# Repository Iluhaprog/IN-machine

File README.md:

> [!NOTE]
> Данный проект является учебным и предназначен в первую очередь для того
> чтобы разобраться и понять как работает вычислительное устройство на самом 
> низком уровне.

В данный момент проект на стадии разработки печатных плат и сборки физического 
устройства. 

Сейчас уже созданы и заказанны платы для АЛУ и Регистра флагов.

В процессе создания блок пользовательских регистров и счетчики команд и микро команд.

Сейчас в планы входят:
- [ ] - доработать схему управляющего устройства для работы с LCD 12864 экраном по SPI
- [ ] - разработка платы расширения для того, чтобы данное вычислительно устройство могло работать с датчиками.
- [ ] - изучение возможностей данного устройства и его параметров

Более подробно о базовых возможностях данного вычислительного устройства можно узнать в директории docs/

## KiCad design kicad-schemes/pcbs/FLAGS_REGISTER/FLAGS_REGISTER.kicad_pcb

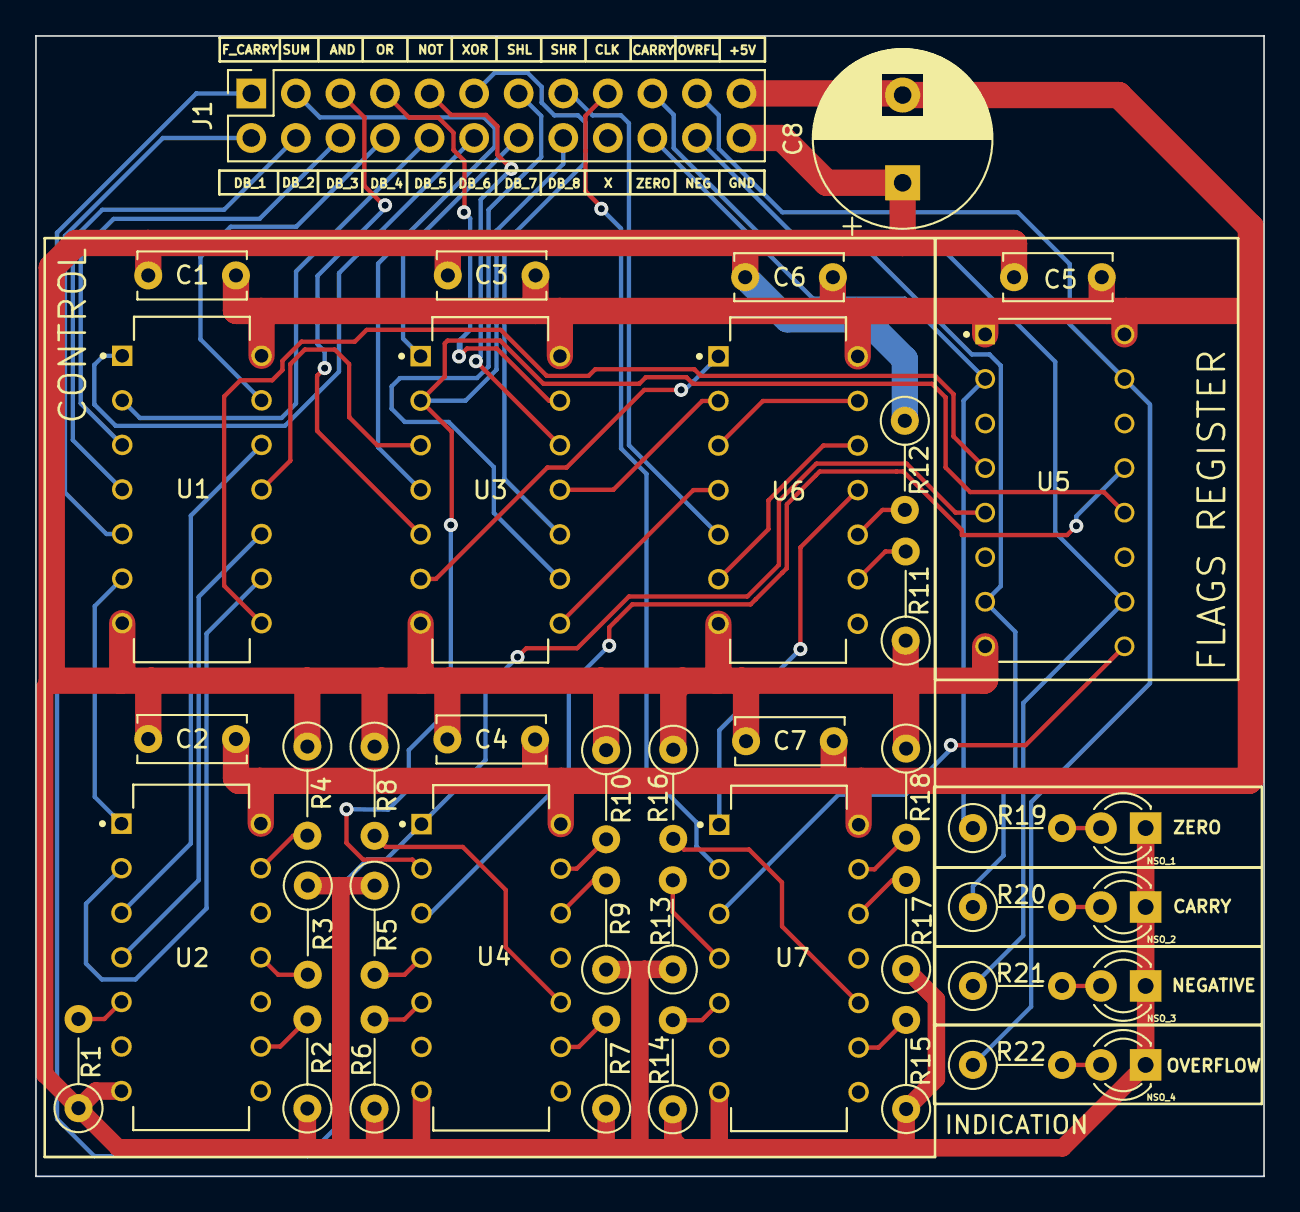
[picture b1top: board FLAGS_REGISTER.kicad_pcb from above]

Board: 2 copper layers, 70.0 x 65.0 mm, 42 parts (0 on the bottom side), 59 nets.

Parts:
C1, C2, C3, C4, C5, C6, C7: C; C_Disc_D6.0mm_W2.5mm_P5.00mm
C8: C; CP_Radial_D10.0mm_P5.00mm
J1: Conn_02x12_Odd_Even; PinSocket_2x12_P2.54mm_Vertical
NSO_1, NSO_2, NSO_3, NSO_4: LED; LED_D3.0mm
R1, R2, R3, R4, R5, R6, R7, R8, R9, R10, R11, R12, R13, R14, R15, R16, R17, R18, R19, R20, R21, R22: R; R_Axial_DIN0207_L6.3mm_D2.5mm_P5.08mm_Vertical
U1: SN74HC27N; DIP794W45P254L1969H508Q14
U2: SN74HC14N; DIP794W45P254L1969H508Q14
U3, U6: SN74HC32N; DIP794W45P254L1969H508Q14
U4: SN74HC86N; DIP794W45P254L1969H508Q14
U5: SN74HC175N; DIP794W45P254L1969H508Q16
U7: SN74HC08N; DIP794W45P254L1969H508Q14

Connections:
+5V: C1.2, C2.2, C3.2, C4.2, C5.2, C6.2, C7.2, C8.2, J1.23, U1.14 (VCC), U2.14 (VCC), U3.14 (VCC), U4.14 (VCC), U5.1 (~CLR), U5.16 (VCC), U6.14 (VCC), U7.14 (VCC)
/CARRY: J1.19, R20.1, U5.7 (2Q)
/CLK: J1.17, U7.2 (1B)
/DB_1: J1.2, U1.5 (2C)
/DB_2: J1.4, U1.4 (2B)
/DB_3: J1.6, U1.3 (2A)
/DB_4: J1.8, U1.13 (1C)
/DB_5: J1.10, U1.2 (1B)
/DB_6: J1.12, U1.1 (1A)
/DB_7: J1.14, U3.1 (1A)
/DB_8: J1.16, U3.2 (1B), U4.2 (1B), U5.12 (3D)
/F_CARRY: J1.1, U4.1 (1A), U5.5 (2D)
/NEGATIVE: J1.22, R21.1, U5.10 (3Q)
/OVERFLOW: J1.21, R22.1, U5.15 (4Q)
/ZERO: J1.20, R19.1, U5.2 (1Q)
/n_AND_EN: J1.5, U3.5 (2B)
/n_NOT_EN: J1.9, U3.12 (4A)
/n_OR_EN: J1.7, U3.13 (4B)
/n_SHL_EN: J1.13, U3.9 (3A)
/n_SHR_EN: J1.15, U6.5 (2B)
/n_SUM_EN: J1.3, U3.4 (2A)
/n_XOR_EN: J1.11, U3.10 (3B)
CLK_FLAGS: U5.9 (CLK), U7.3 (1Y)
EN_WRITE_FLAGS: U6.11 (4Y), U7.1 (1A)
F_OVERFLOW: U4.3 (1Y), U5.13 (4D)
F_ZERO: U1.8 (3Y), U5.4 (1D)
GND: C1.1, C2.1, C3.1, C4.1, C5.1, C6.1, C7.1, C8.1, J1.24, NSO_1.1 (K), NSO_2.1 (K), NSO_3.1 (K), NSO_4.1 (K), R1.1, R2.1, R3.1, R4.1, R5.1, R6.1, R7.1, R8.1, R9.1, R10.1, R11.1, R12.1, R13.1, R14.1, R15.1, R16.1, R17.1, R18.1, U1.7 (GND), U2.7 (GND), U3.7 (GND), U4.7 (GND), U5.8 (GND), U6.7 (GND), U7.7 (GND)
NOT_OR_OR: U3.11 (4Y), U6.2 (1B)
unnamed: NSO_1.2 (A), R19.2
unnamed: NSO_2.2 (A), R20.2
unnamed: NSO_3.2 (A), R21.2
unnamed: NSO_4.2 (A), R22.2
unnamed: R1.2, U2.5 (3A)
unnamed: R2.2, U2.9 (4A)
unnamed: R3.2, U2.11 (5A)
unnamed: R4.2, U2.13 (6A)
unnamed: R5.2, U4.4 (2A)
unnamed: R6.2, U4.5 (2B)
unnamed: R7.2, U4.9 (3A)
unnamed: R8.2, U4.10 (3B)
unnamed: R9.2, U4.12 (4A)
unnamed: R10.2, U4.13 (4B)
unnamed: R11.2, U6.9 (3A)
unnamed: R12.2, U6.10 (3B)
unnamed: R13.2, U7.4 (2A)
unnamed: R14.2, U7.5 (2B)
unnamed: R15.2, U7.9 (3A)
unnamed: R16.2, U7.10 (3B)
unnamed: R17.2, U7.12 (4A)
unnamed: R18.2, U7.13 (4B)
O1_O2_O3: U1.6 (2Y), U2.1 (1A)
O4_O5_O6: U1.12 (1Y), U2.3 (2A)
SUM_OR_AND: U3.6 (2Y), U6.1 (1A)
SUM_OR_AND_OR_NOT_OR_OR: U6.3 (1Y), U6.13 (4B)
XOR_OR_SHL: U3.8 (3Y), U6.4 (2A)
XOR_OR_SHL_OR_SHR: U6.6 (2Y), U6.12 (4A)
n_O1_O2_O3: U1.9 (3A), U2.2 (1Y)
n_O4_O5_O6: U1.10 (3B), U2.4 (2Y)
n_O7_O8: U1.11 (3C), U3.3 (1Y)

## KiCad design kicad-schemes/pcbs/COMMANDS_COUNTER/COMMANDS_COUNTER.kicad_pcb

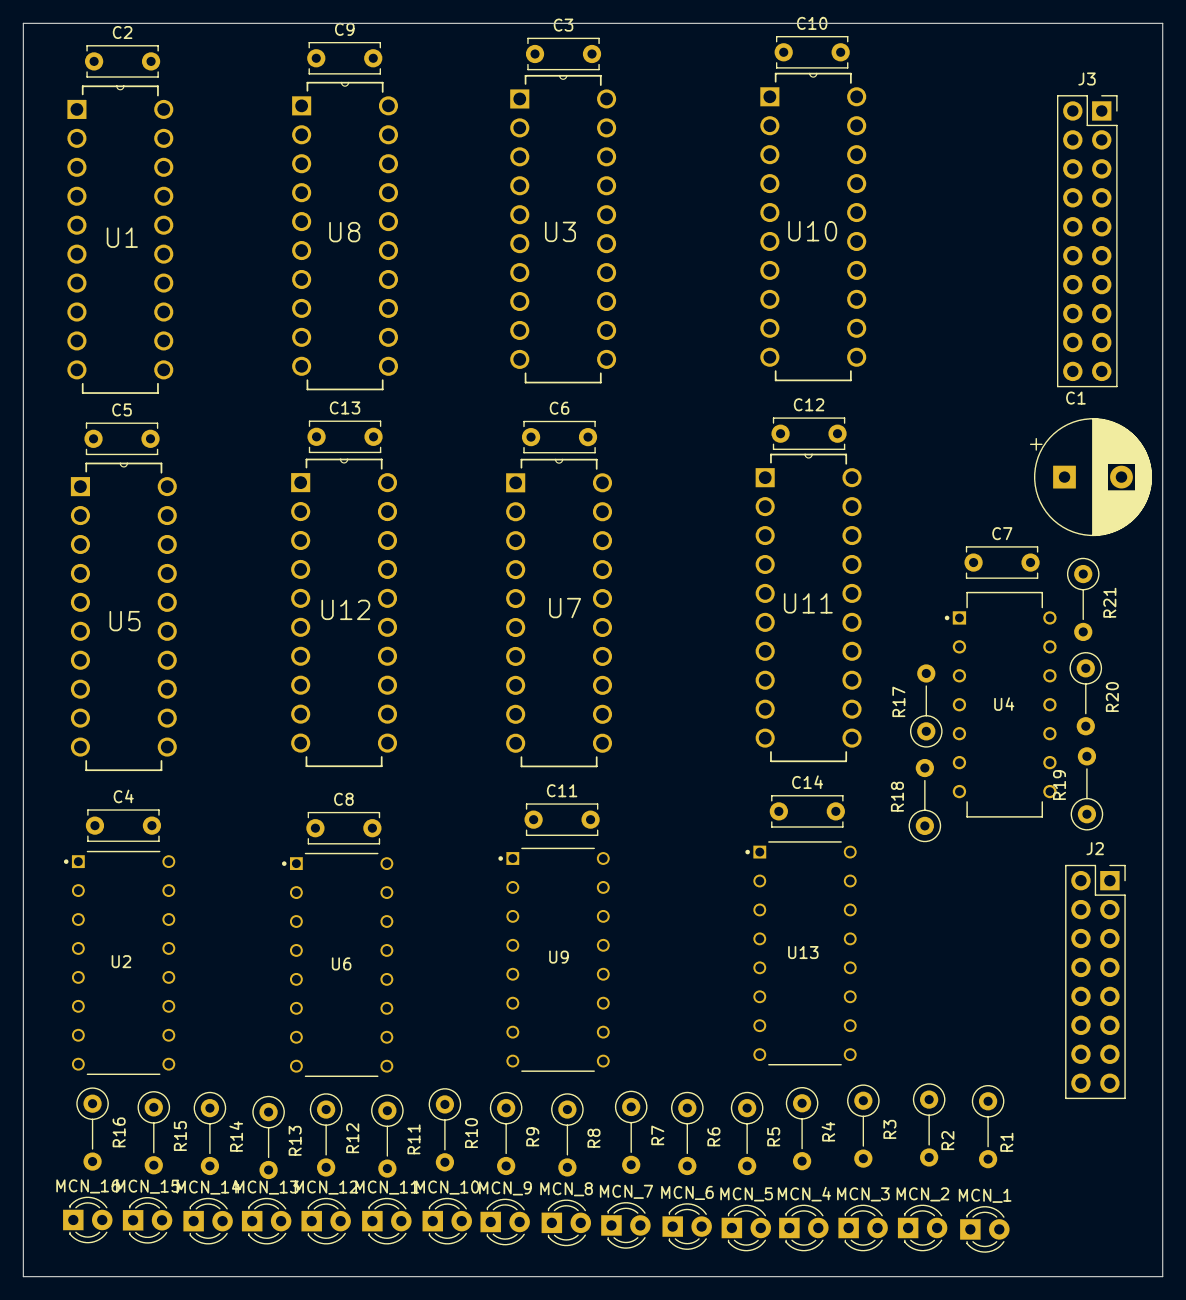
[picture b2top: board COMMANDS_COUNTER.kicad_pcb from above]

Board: 2 copper layers, 100.0 x 110.0 mm, 66 parts (0 on the bottom side), 109 nets, no tracks yet.

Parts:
C1: C; CP_Radial_D10.0mm_P5.00mm
C2, C3, C4, C5, C6, C7, C8, C9, C10, C11, C12, C13, C14: C; C_Disc_D6.0mm_W2.5mm_P5.00mm
J2: Conn_02x08_Odd_Even; PinSocket_2x08_P2.54mm_Vertical
J3: Conn_02x10_Odd_Even; PinSocket_2x10_P2.54mm_Vertical
MCN_1, MCN_2, MCN_3, MCN_4, MCN_5, MCN_6, MCN_7, MCN_8, MCN_9, MCN_10, MCN_11, MCN_12, MCN_13, MCN_14, MCN_15, MCN_16: LED; LED_D3.0mm
R1, R2, R3, R4, R5, R6, R7, R8, R9, R10, R11, R12, R13, R14, R15, R16, R17, R18, R19, R20, R21: R; R_Axial_DIN0207_L6.3mm_D2.5mm_P5.08mm_Vertical
U1, U3, U8, U10: SN74HC377N; DIP254P762X508-20
U2, U6, U9, U13: SN74HC163N; DIP794W45P254L1969H508Q16
U4: SN74HC14N; DIP794W45P254L1969H508Q14
U5, U7, U11, U12: SN74HC244N; DIP254P762X508-20

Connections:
/AB1: J2.1, R1.1, U2.14 (QA), U3.3 (1D)
/AB2: J2.3, R2.1, U2.13 (QB), U3.4 (2D)
/AB3: J2.5, R3.1, U2.12 (QC), U3.7 (3D)
/AB4: J2.7, R4.1, U2.11 (QD), U3.8 (4D)
/AB5: J2.9, R5.1, U3.13 (5D), U6.14 (QA)
/AB6: J2.11, R6.1, U3.14 (6D), U6.13 (QB)
/AB7: J2.13, R7.1, U3.17 (7D), U6.12 (QC)
/AB8: J2.15, R8.1, U3.18 (8D), U6.11 (QD)
/AB9: J2.2, R9.1, U9.14 (QA), U10.3 (1D)
/AB10: J2.4, R10.1, U9.13 (QB), U10.4 (2D)
/AB11: J2.6, R11.1, U9.12 (QC), U10.7 (3D)
/AB12: J2.8, R12.1, U9.11 (QD), U10.8 (4D)
/AB13: J2.10, R13.1, U10.13 (5D), U13.14 (QA)
/AB14: J2.12, R14.1, U10.14 (6D), U13.13 (QB)
/AB15: J2.14, R15.1, U10.17 (7D), U13.12 (QC)
/AB16: J2.16, R16.1, U10.18 (8D), U13.11 (QD)
/CAR_n_EN1: J3.18, U3.1 (~CLKEN)
/CAR_n_EN2: J3.20, U10.1 (~CLKEN)
/CAR_n_EN_Out: J3.16, U7.1 (1~OE), U7.19 (2~OE), U11.1 (1~OE), U11.19 (2~OE)
/C_n_Clear: J3.4, U2.1 (~CLR), U6.1 (~CLR), U9.1 (~CLR), U13.1 (~CLR)
/C_n_Enable_Counter: J3.2, U2.7 (ENP), U6.7 (ENP), U9.7 (ENP), U13.7 (ENP)
/C_n_Enable_Load: J3.6, U2.9 (~LOAD), U6.9 (~LOAD), U9.9 (~LOAD), U13.9 (~LOAD)
/DB1: J3.5, U1.13 (5D), U8.13 (5D)
/DB2: J3.7, U1.8 (4D), U8.8 (4D)
/DB3: J3.9, U1.14 (6D), U8.14 (6D)
/DB4: J3.11, U1.7 (3D), U8.7 (3D)
/DB5: J3.13, U1.17 (7D), U8.17 (7D)
/DB6: J3.15, U1.4 (2D), U8.4 (2D)
/DB7: J3.17, U1.18 (8D), U8.18 (8D)
/DB8: J3.19, U1.3 (1D), U8.3 (1D)
/GND: C1.1, C2.1, C3.1, C4.1, C5.1, C6.1, C7.1, C8.1, C9.1, C10.1, C11.1, C12.1, C13.1, C14.1, J3.1, MCN_1.1 (K), MCN_2.1 (K), MCN_3.1 (K), MCN_4.1 (K), MCN_5.1 (K), MCN_6.1 (K), MCN_7.1 (K), MCN_8.1 (K), MCN_9.1 (K), MCN_10.1 (K), MCN_11.1 (K), MCN_12.1 (K), MCN_13.1 (K), MCN_14.1 (K), MCN_15.1 (K), MCN_16.1 (K), R17.1, R18.1, R19.1, R20.1, R21.1, U1.10 (GND), U2.8 (GND), U3.10 (GND), U4.7 (GND), U5.10 (GND), U6.8 (GND), U7.10 (GND), U8.10 (GND), U9.8 (GND), U10.10 (GND), U11.10 (GND), U12.10 (GND), U13.8 (GND)
/POWER: C1.2, C2.2, C3.2, C4.2, C5.2, C6.2, C7.2, C8.2, C9.2, C10.2, C11.2, C12.2, C13.2, C14.2, J3.3, U1.20 (VCC), U2.10 (ENT), U2.16 (VCC), U3.20 (VCC), U4.14 (VCC), U5.20 (VCC), U6.16 (VCC), U7.20 (VCC), U8.20 (VCC), U9.16 (VCC), U10.20 (VCC), U11.20 (VCC), U12.20 (VCC), U13.16 (VCC)
/UAR_n_EN1: J3.8, U1.1 (~CLKEN)
/UAR_n_EN2: J3.10, U8.1 (~CLKEN)
/UAR_n_EN_Out: J3.12, U5.1 (1~OE), U5.19 (2~OE), U12.1 (1~OE), U12.19 (2~OE)
CLK: J3.14, U1.11 (CLK), U2.2 (CLK), U4.1 (1A), U6.2 (CLK), U8.11 (CLK), U9.2 (CLK), U13.2 (CLK)
CR_O_1: U2.3 (A), U5.3 (2Y4), U7.18 (1Y1)
CR_O_2: U2.4 (B), U5.18 (1Y1), U7.16 (1Y2)
CR_O_3: U2.5 (C), U5.5 (2Y3), U7.14 (1Y3)
CR_O_4: U2.6 (D), U5.16 (1Y2), U7.12 (1Y4)
CR_O_5: U5.7 (2Y2), U6.3 (A), U7.9 (2Y1)
CR_O_6: U5.14 (1Y3), U6.4 (B), U7.7 (2Y2)
CR_O_7: U5.9 (2Y1), U6.5 (C), U7.5 (2Y3)
CR_O_8: U5.12 (1Y4), U6.6 (D), U7.3 (2Y4)
CR_O_9: U9.3 (A), U11.18 (1Y1), U12.3 (2Y4)
CR_O_10: U9.4 (B), U11.16 (1Y2), U12.18 (1Y1)
CR_O_11: U9.5 (C), U11.14 (1Y3), U12.5 (2Y3)
CR_O_12: U9.6 (D), U11.12 (1Y4), U12.16 (1Y2)
CR_O_13: U11.9 (2Y1), U12.7 (2Y2), U13.3 (A)
CR_O_14: U11.7 (2Y2), U12.14 (1Y3), U13.4 (B)
CR_O_15: U11.5 (2Y3), U12.9 (2Y1), U13.5 (C)
CR_O_16: U11.3 (2Y4), U12.12 (1Y4), U13.6 (D)
C_RCO_1: U2.15 (RCO), U6.10 (ENT)
C_RCO_2: U6.15 (RCO), U9.10 (ENT)
C_RCO_3: U9.15 (RCO), U13.10 (ENT)
unnamed: MCN_1.2 (A), R1.2
unnamed: MCN_2.2 (A), R2.2
unnamed: MCN_3.2 (A), R3.2
unnamed: MCN_4.2 (A), R4.2
unnamed: MCN_5.2 (A), R5.2
unnamed: MCN_6.2 (A), R6.2
unnamed: MCN_7.2 (A), R7.2
unnamed: MCN_8.2 (A), R8.2
unnamed: MCN_9.2 (A), R9.2
unnamed: MCN_10.2 (A), R10.2
unnamed: MCN_11.2 (A), R11.2
unnamed: MCN_12.2 (A), R12.2
unnamed: MCN_13.2 (A), R13.2
unnamed: MCN_14.2 (A), R14.2
unnamed: MCN_15.2 (A), R15.2
unnamed: MCN_16.2 (A), R16.2
unnamed: R17.2, U4.3 (2A)
unnamed: R18.2, U4.5 (3A)
unnamed: R19.2, U4.9 (4A)
unnamed: R20.2, U4.11 (5A)
unnamed: R21.2, U4.13 (6A)
in_UAR_O_1: U1.12 (5Q), U5.17 (2A4)
in_UAR_O_2: U1.9 (4Q), U5.2 (1A1)
in_UAR_O_3: U1.15 (6Q), U5.15 (2A3)
in_UAR_O_4: U1.6 (3Q), U5.4 (1A2)
in_UAR_O_5: U1.16 (7Q), U5.13 (2A2)
in_UAR_O_6: U1.5 (2Q), U5.6 (1A3)
in_UAR_O_7: U1.19 (8Q), U5.11 (2A1)
in_UAR_O_8: U1.2 (1Q), U5.8 (1A4)
in_UAR_O_9: U8.12 (5Q), U12.17 (2A4)
in_UAR_O_10: U8.9 (4Q), U12.2 (1A1)
in_UAR_O_11: U8.15 (6Q), U12.15 (2A3)
in_UAR_O_12: U8.6 (3Q), U12.4 (1A2)
in_UAR_O_13: U8.16 (7Q), U12.13 (2A2)
in_UAR_O_14: U8.5 (2Q), U12.6 (1A3)
in_UAR_O_15: U8.19 (8Q), U12.11 (2A1)
in_UAR_O_16: U8.2 (1Q), U12.8 (1A4)
in_СAR_O_1: U3.2 (1Q), U7.2 (1A1)
in_СAR_O_2: U3.5 (2Q), U7.4 (1A2)
in_СAR_O_3: U3.6 (3Q), U7.6 (1A3)
in_СAR_O_4: U3.9 (4Q), U7.8 (1A4)
in_СAR_O_5: U3.12 (5Q), U7.11 (2A1)
in_СAR_O_6: U3.15 (6Q), U7.13 (2A2)
in_СAR_O_7: U3.16 (7Q), U7.15 (2A3)
in_СAR_O_8: U3.19 (8Q), U7.17 (2A4)
in_СAR_O_9: U10.2 (1Q), U11.2 (1A1)
in_СAR_O_10: U10.5 (2Q), U11.4 (1A2)
in_СAR_O_11: U10.6 (3Q), U11.6 (1A3)
in_СAR_O_12: U10.9 (4Q), U11.8 (1A4)
in_СAR_O_13: U10.12 (5Q), U11.11 (2A1)
in_СAR_O_14: U10.15 (6Q), U11.13 (2A2)
in_СAR_O_15: U10.16 (7Q), U11.15 (2A3)
in_СAR_O_16: U10.19 (8Q), U11.17 (2A4)
n_CLK: U3.11 (CLK), U4.2 (1Y), U10.11 (CLK)

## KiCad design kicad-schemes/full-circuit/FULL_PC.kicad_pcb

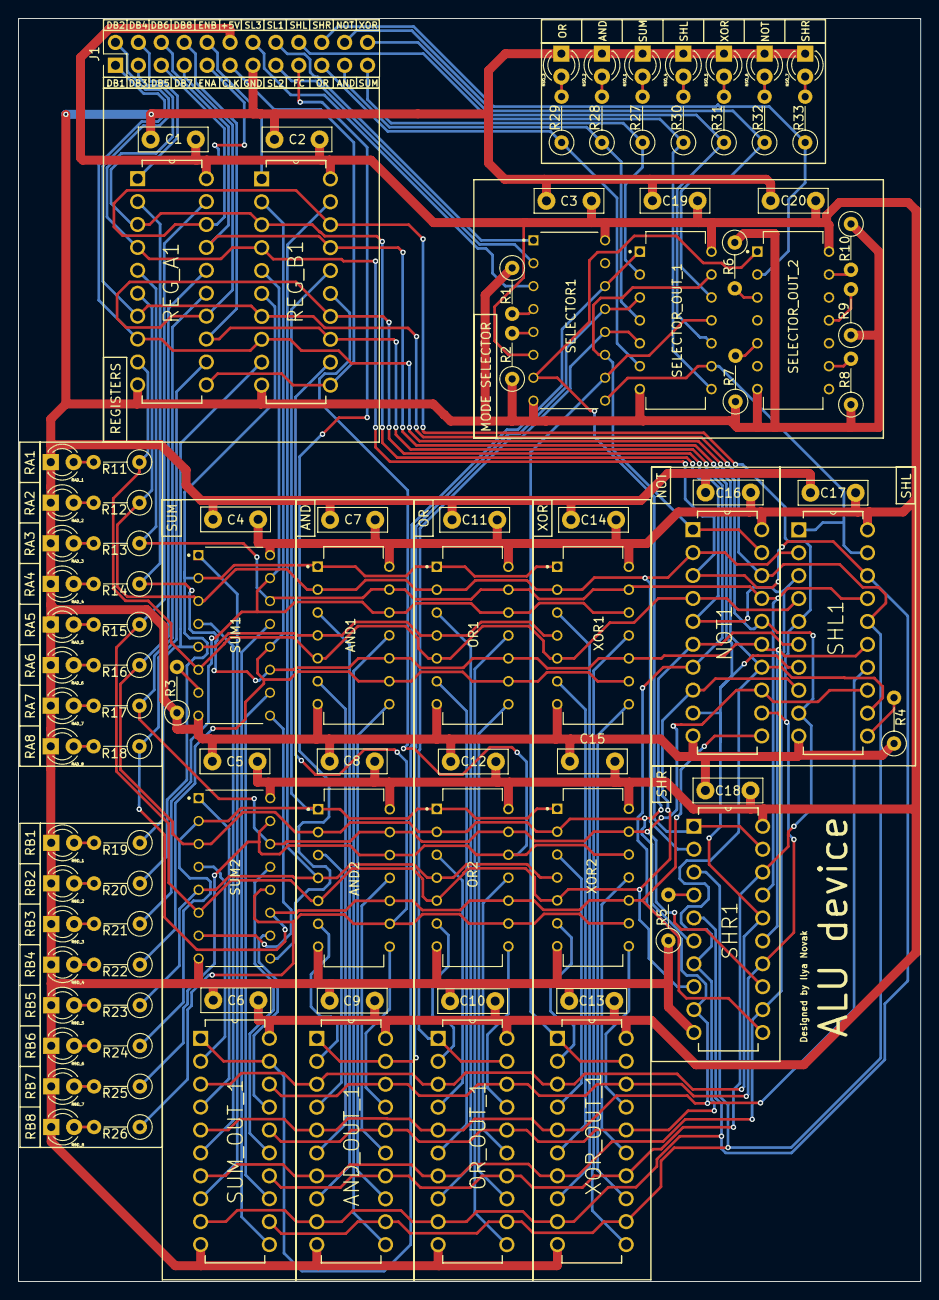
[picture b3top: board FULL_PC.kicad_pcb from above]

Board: 2 copper layers, 100.0 x 140.0 mm, 97 parts (0 on the bottom side), 113 nets.

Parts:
AND1, AND2: SN74HC08N; DIP794W45P254L1969H508Q14
AND_OUT_1: SN74HC244N; DIP254P762X508-20
C1, C2, C3, C4, C5, C6, C7, C8, C9, C10, C11, C12, C13, C14, C15, C16, C17, C18, C19, C20: C; C_Disc_D7.5mm_W2.5mm_P5.00mm
J1: Conn_02x12_Counter_Clockwise; PinHeader_2x12_P2.54mm_Vertical
NOT1: SN74HC240N; DIP254P762X508-20
NSO_1, NSO_2, NSO_3, NSO_4, NSO_5, NSO_6, NSO_7: LED; LED_D3.0mm
OR1, OR2: SN74HC32N; DIP794W45P254L1969H508Q14
OR_OUT_1: SN74HC244N; DIP254P762X508-20
R1, R2, R3, R4, R5, R6, R7, R8, R9, R10, R11, R12, R13, R14, R15, R16, R17, R18, R19, R20, R21, R22, R23, R24, R25, R26, R27, R28, R29, R30, R31, R32, R33: R; R_Axial_DIN0207_L6.3mm_D2.5mm_P5.08mm_Vertical
RAD_1, RAD_2, RAD_3, RAD_4, RAD_5, RAD_6, RAD_7, RAD_8: LED; LED_D3.0mm
RBD_1, RBD_2, RBD_3, RBD_4, RBD_5, RBD_6, RBD_7, RBD_8: LED; LED_D3.0mm
REG_A1: SN74HC377N; DIP254P762X508-20
REG_B1: SN74HC377N; DIP254P762X508-20
SELECTOR1: SN74HC138N; DIP794W45P254L1969H508Q16
SELECTOR_OUT_1, SELECTOR_OUT_2: SN74HC14N; DIP794W45P254L1969H508Q14
SHL1: SN74HC244N; DIP254P762X508-20
SHR1: SN74HC244N; DIP254P762X508-20
SUM1, SUM2: SN74HC283N; DIP794W45P254L1969H508Q16
SUM_OUT_1: SN74HC244N; DIP254P762X508-20
XOR1, XOR2: SN74HC86N; DIP794W45P254L1969H508Q14
XOR_OUT_1: SN74HC244N; DIP254P762X508-20

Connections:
+5V: AND1.14 (VCC), AND2.14 (VCC), AND_OUT_1.20 (VCC), C1.2, C2.2, C3.2, C4.2, C5.2, C6.2, C7.2, C8.2, C9.2, C10.2, C11.2, C12.2, C13.2, C14.2, C15.2, C16.2, C17.2, C18.2, C19.2, C20.2, J1.12, NOT1.20 (VCC), OR1.14 (VCC), OR2.14 (VCC), OR_OUT_1.20 (VCC), REG_A1.20 (VCC), REG_B1.20 (VCC), SELECTOR1.6 (G1), SELECTOR1.16 (VCC), SELECTOR_OUT_1.14 (VCC), SELECTOR_OUT_2.14 (VCC), SHL1.20 (VCC), SHR1.20 (VCC), SUM1.16 (Vcc), SUM2.16 (Vcc), SUM_OUT_1.20 (VCC), XOR1.14 (VCC), XOR2.14 (VCC), XOR_OUT_1.20 (VCC)
/ALU/CLK: J1.11, REG_A1.11 (CLK), REG_B1.11 (CLK)
/ALU/DB_1: AND_OUT_1.14 (1Y3), J1.1, NOT1.16 (1Y2), OR_OUT_1.14 (1Y3), REG_A1.8 (4D), REG_B1.8 (4D), SHL1.9 (2Y1), SHR1.18 (1Y1), SUM_OUT_1.14 (1Y3), XOR_OUT_1.14 (1Y3)
/ALU/DB_2: AND_OUT_1.12 (1Y4), J1.2, NOT1.18 (1Y1), OR_OUT_1.12 (1Y4), REG_A1.7 (3D), REG_B1.7 (3D), SHL1.16 (1Y2), SHR1.3 (2Y4), SUM_OUT_1.12 (1Y4), XOR_OUT_1.12 (1Y4)
/ALU/DB_3: AND_OUT_1.9 (2Y1), J1.3, NOT1.3 (2Y4), OR_OUT_1.9 (2Y1), REG_A1.4 (2D), REG_B1.4 (2D), SHL1.18 (1Y1), SHR1.5 (2Y3), SUM_OUT_1.9 (2Y1), XOR_OUT_1.9 (2Y1)
/ALU/DB_4: AND_OUT_1.7 (2Y2), J1.4, NOT1.5 (2Y3), OR_OUT_1.7 (2Y2), REG_A1.3 (1D), REG_B1.3 (1D), SHL1.3 (2Y4), SHR1.12 (1Y4), SUM_OUT_1.7 (2Y2), XOR_OUT_1.7 (2Y2)
/ALU/DB_5: AND_OUT_1.18 (1Y1), J1.5, NOT1.12 (1Y4), OR_OUT_1.18 (1Y1), REG_A1.18 (8D), REG_B1.18 (8D), SHL1.5 (2Y3), SHR1.14 (1Y3), SUM_OUT_1.18 (1Y1), XOR_OUT_1.18 (1Y1)
/ALU/DB_6: AND_OUT_1.16 (1Y2), J1.6, NOT1.14 (1Y3), OR_OUT_1.16 (1Y2), REG_A1.17 (7D), REG_B1.17 (7D), SHL1.12 (1Y4), SHR1.7 (2Y2), SUM_OUT_1.16 (1Y2), XOR_OUT_1.16 (1Y2)
/ALU/DB_7: AND_OUT_1.5 (2Y3), J1.7, NOT1.7 (2Y2), OR_OUT_1.5 (2Y3), REG_A1.14 (6D), REG_B1.14 (6D), SHL1.14 (1Y3), SHR1.9 (2Y1), SUM_OUT_1.5 (2Y3), XOR_OUT_1.5 (2Y3)
/ALU/DB_8: AND_OUT_1.3 (2Y4), J1.8, NOT1.9 (2Y1), OR_OUT_1.3 (2Y4), REG_A1.13 (5D), REG_B1.13 (5D), SHL1.7 (2Y2), SHR1.16 (1Y2), SUM_OUT_1.3 (2Y4), XOR_OUT_1.3 (2Y4)
/ALU/EN_A: J1.9, REG_A1.1 (~CLKEN)
/ALU/EN_B: J1.10, REG_B1.1 (~CLKEN)
/ALU/F_CARRY: J1.17, SUM2.9 (C4)
/ALU/SL_1: J1.16, SELECTOR1.1 (A)
/ALU/SL_2: J1.15, SELECTOR1.2 (B)
/ALU/SL_3: J1.14, SELECTOR1.3 (C)
/ALU/n_AND_EN: J1.21, R28.1, SELECTOR_OUT_1.4 (2Y)
/ALU/n_NOT_EN: J1.22, R32.1, SELECTOR_OUT_1.12 (6Y)
/ALU/n_OR_EN: J1.19, R29.1, SELECTOR_OUT_1.6 (3Y)
/ALU/n_SHL_EN: J1.18, R30.1, SELECTOR_OUT_1.8 (4Y)
/ALU/n_SHR_EN: J1.20, R33.1, SELECTOR_OUT_2.2 (1Y)
/ALU/n_SUM_EN: J1.23, R27.1, SELECTOR_OUT_1.2 (1Y)
/ALU/n_XOR_EN: J1.24, R31.1, SELECTOR_OUT_1.10 (5Y)
AND_EN: AND_OUT_1.1 (1~OE), AND_OUT_1.19 (2~OE), SELECTOR1.13 (Y2), SELECTOR_OUT_1.3 (2A)
AND_O_1: AND1.6 (2Y), AND_OUT_1.6 (1A3)
AND_O_2: AND1.3 (1Y), AND_OUT_1.8 (1A4)
AND_O_3: AND1.11 (4Y), AND_OUT_1.11 (2A1)
AND_O_4: AND1.8 (3Y), AND_OUT_1.13 (2A2)
AND_O_5: AND2.6 (2Y), AND_OUT_1.2 (1A1)
AND_O_6: AND2.3 (1Y), AND_OUT_1.4 (1A2)
AND_O_7: AND2.11 (4Y), AND_OUT_1.15 (2A3)
AND_O_8: AND2.8 (3Y), AND_OUT_1.17 (2A4)
GND: AND1.7 (GND), AND2.7 (GND), AND_OUT_1.10 (GND), C1.1, C2.1, C3.1, C4.1, C5.1, C6.1, C7.1, C8.1, C9.1, C10.1, C11.1, C12.1, C13.1, C14.1, C15.1, C16.1, C17.1, C18.1, C19.1, C20.1, J1.13, NOT1.10 (GND), NSO_1.1 (K), NSO_2.1 (K), NSO_3.1 (K), NSO_4.1 (K), NSO_5.1 (K), NSO_6.1 (K), NSO_7.1 (K), OR1.7 (GND), OR2.7 (GND), OR_OUT_1.10 (GND), R1.1, R2.1, R3.1, R4.1, R5.1, R6.1, R7.1, R8.1, R9.1, R10.1, RAD_1.1 (K), RAD_2.1 (K), RAD_3.1 (K), RAD_4.1 (K), RAD_5.1 (K), RAD_6.1 (K), RAD_7.1 (K), RAD_8.1 (K), RBD_1.1 (K), RBD_2.1 (K), RBD_3.1 (K), RBD_4.1 (K), RBD_5.1 (K), RBD_6.1 (K), RBD_7.1 (K), RBD_8.1 (K), REG_A1.10 (GND), REG_B1.10 (GND), SELECTOR1.8 (GND), SELECTOR_OUT_1.7 (GND), SELECTOR_OUT_2.7 (GND), SHL1.10 (GND), SHR1.10 (GND), SUM1.8 (GND), SUM2.8 (GND), SUM_OUT_1.10 (GND), XOR1.7 (GND), XOR2.7 (GND), XOR_OUT_1.10 (GND)
NOT_EN: NOT1.1 (1~OE), NOT1.19 (2~OE), SELECTOR1.11 (Y4), SELECTOR_OUT_1.13 (6A)
unnamed: NSO_1.2 (A), R27.2
unnamed: NSO_2.2 (A), R28.2
unnamed: NSO_3.2 (A), R29.2
unnamed: NSO_4.2 (A), R30.2
unnamed: NSO_5.2 (A), R31.2
unnamed: NSO_6.2 (A), R32.2
unnamed: NSO_7.2 (A), R33.2
unnamed: R11.2, RAD_1.2 (A)
unnamed: R12.2, RAD_2.2 (A)
unnamed: R13.2, RAD_3.2 (A)
unnamed: R14.2, RAD_4.2 (A)
unnamed: R15.2, RAD_5.2 (A)
unnamed: R16.2, RAD_6.2 (A)
unnamed: R17.2, RAD_7.2 (A)
unnamed: R18.2, RAD_8.2 (A)
unnamed: R19.2, RBD_1.2 (A)
unnamed: R20.2, RBD_2.2 (A)
unnamed: R21.2, RBD_3.2 (A)
unnamed: R22.2, RBD_4.2 (A)
unnamed: R23.2, RBD_5.2 (A)
unnamed: R24.2, RBD_6.2 (A)
unnamed: R25.2, RBD_7.2 (A)
unnamed: R26.2, RBD_8.2 (A)
unnamed: R1.2, SELECTOR1.4 (~G2A)
unnamed: R2.2, SELECTOR1.5 (~G2B)
unnamed: R6.2, SELECTOR_OUT_2.3 (2A)
unnamed: R7.2, SELECTOR_OUT_2.5 (3A)
unnamed: R8.2, SELECTOR_OUT_2.9 (4A)
unnamed: R9.2, SELECTOR_OUT_2.11 (5A)
unnamed: R10.2, SELECTOR_OUT_2.13 (6A)
unnamed: R4.2, SHL1.11 (2A1)
unnamed: R5.2, SHR1.4 (1A2)
unnamed: R3.2, SUM1.7 (C0)
unnamed: SUM1.9 (C4), SUM2.7 (C0)
OR_EN: OR_OUT_1.1 (1~OE), OR_OUT_1.19 (2~OE), SELECTOR1.12 (Y3), SELECTOR_OUT_1.5 (3A)
OR_O_1: OR1.6 (2Y), OR_OUT_1.6 (1A3)
OR_O_2: OR1.3 (1Y), OR_OUT_1.8 (1A4)
OR_O_3: OR1.11 (4Y), OR_OUT_1.11 (2A1)
OR_O_4: OR1.8 (3Y), OR_OUT_1.13 (2A2)
OR_O_5: OR2.6 (2Y), OR_OUT_1.2 (1A1)
OR_O_6: OR2.3 (1Y), OR_OUT_1.4 (1A2)
OR_O_7: OR2.11 (4Y), OR_OUT_1.15 (2A3)
OR_O_8: OR2.8 (3Y), OR_OUT_1.17 (2A4)
RA_1: AND1.5 (2B), NOT1.4 (1A2), OR1.5 (2B), R11.1, REG_A1.9 (4Q), SHL1.4 (1A2), SUM1.6 (B1), XOR1.5 (2B)
RA_2: AND1.2 (1B), NOT1.2 (1A1), OR1.2 (1B), R12.1, REG_A1.6 (3Q), SHL1.2 (1A1), SHR1.2 (1A1), SUM1.3 (A2), XOR1.2 (1B)
RA_3: AND1.13 (4B), NOT1.17 (2A4), OR1.13 (4B), R13.1, REG_A1.5 (2Q), SHL1.17 (2A4), SHR1.17 (2A4), SUM1.14 (A3), XOR1.13 (4B)
RA_4: AND1.10 (3B), NOT1.15 (2A3), OR1.10 (3B), R14.1, REG_A1.2 (1Q), SHL1.15 (2A3), SHR1.15 (2A3), SUM1.11 (B4), XOR1.10 (3B)
RA_5: AND2.5 (2B), NOT1.8 (1A4), OR2.5 (2B), R15.1, REG_A1.19 (8Q), SHL1.8 (1A4), SHR1.8 (1A4), SUM2.6 (B1), XOR2.5 (2B)
RA_6: AND2.2 (1B), NOT1.6 (1A3), OR2.2 (1B), R16.1, REG_A1.16 (7Q), SHL1.6 (1A3), SHR1.6 (1A3), SUM2.3 (A2), XOR2.2 (1B)
RA_7: AND2.13 (4B), NOT1.13 (2A2), OR2.13 (4B), R17.1, REG_A1.15 (6Q), SHL1.13 (2A2), SHR1.13 (2A2), SUM2.14 (A3), XOR2.13 (4B)
RA_8: AND2.10 (3B), NOT1.11 (2A1), OR2.10 (3B), R18.1, REG_A1.12 (5Q), SHR1.11 (2A1), SUM2.11 (B4), XOR2.10 (3B)
RB_1: AND1.4 (2A), OR1.4 (2A), R19.1, REG_B1.9 (4Q), SUM1.5 (A1), XOR1.4 (2A)
RB_2: AND1.1 (1A), OR1.1 (1A), R20.1, REG_B1.6 (3Q), SUM1.2 (B2), XOR1.1 (1A)
RB_3: AND1.12 (4A), OR1.12 (4A), R21.1, REG_B1.5 (2Q), SUM1.15 (B3), XOR1.12 (4A)
RB_4: AND1.9 (3A), OR1.9 (3A), R22.1, REG_B1.2 (1Q), SUM1.12 (A4), XOR1.9 (3A)
RB_5: AND2.4 (2A), OR2.4 (2A), R23.1, REG_B1.19 (8Q), SUM2.5 (A1), XOR2.4 (2A)
RB_6: AND2.1 (1A), OR2.1 (1A), R24.1, REG_B1.16 (7Q), SUM2.2 (B2), XOR2.1 (1A)
RB_7: AND2.12 (4A), OR2.12 (4A), R25.1, REG_B1.15 (6Q), SUM2.15 (B3), XOR2.12 (4A)
RB_8: AND2.9 (3A), OR2.9 (3A), R26.1, REG_B1.12 (5Q), SUM2.12 (A4), XOR2.9 (3A)
SHL_EN: SELECTOR1.9 (Y6), SELECTOR_OUT_1.9 (4A), SHL1.1 (1~OE), SHL1.19 (2~OE)
SHR_EN: SELECTOR1.7 (Y7), SELECTOR_OUT_2.1 (1A), SHR1.1 (1~OE), SHR1.19 (2~OE)
SUM_EN: SELECTOR1.14 (Y1), SELECTOR_OUT_1.1 (1A), SUM_OUT_1.1 (1~OE), SUM_OUT_1.19 (2~OE)
SUM_O_1: SUM1.4 (S1), SUM_OUT_1.6 (1A3)
SUM_O_2: SUM1.1 (S2), SUM_OUT_1.8 (1A4)
SUM_O_3: SUM1.13 (S3), SUM_OUT_1.11 (2A1)
SUM_O_4: SUM1.10 (S4), SUM_OUT_1.13 (2A2)
SUM_O_5: SUM2.4 (S1), SUM_OUT_1.2 (1A1)
SUM_O_6: SUM2.1 (S2), SUM_OUT_1.4 (1A2)
SUM_O_7: SUM2.13 (S3), SUM_OUT_1.15 (2A3)
SUM_O_8: SUM2.10 (S4), SUM_OUT_1.17 (2A4)
XOR_EN: SELECTOR1.10 (Y5), SELECTOR_OUT_1.11 (5A), XOR_OUT_1.1 (1~OE), XOR_OUT_1.19 (2~OE)
XOR_O_1: XOR1.6 (2Y), XOR_OUT_1.6 (1A3)
XOR_O_2: XOR1.3 (1Y), XOR_OUT_1.8 (1A4)
XOR_O_3: XOR1.11 (4Y), XOR_OUT_1.11 (2A1)
XOR_O_4: XOR1.8 (3Y), XOR_OUT_1.13 (2A2)
XOR_O_5: XOR2.6 (2Y), XOR_OUT_1.2 (1A1)
XOR_O_6: XOR2.3 (1Y), XOR_OUT_1.4 (1A2)
XOR_O_7: XOR2.11 (4Y), XOR_OUT_1.15 (2A3)
XOR_O_8: XOR2.8 (3Y), XOR_OUT_1.17 (2A4)

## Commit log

2024-01-21 feat: init commit
2024-01-21 feat: Added docs for control unit firmware. Added main logisim model to test firmware. Added tool and description to create and test cu-firmware that created from docs/cu-firmware.
2024-01-21 format: Formatted readme for cfbu tool.
2024-01-21 feat: Added common spec for comuter.
2024-01-21 feat: Added jmasp-transpiler. Added examples and description.
2024-01-21 feat: Added full circuit of pc. Added pcb for alu, because it in full circuit
2024-01-21 feat: Added PCB's for flags register and started commands counters PCB.
2024-01-21 feat: Added common description.
2024-01-21 feat: Added main model modifications that allows create PCB's. This schemes for tests can use build files from tools\jmasm-transpiler\example.
2024-01-21 feat: Added syntax highlighting in nvim.
2024-01-21 feat: Added description for nvim-plugin
2024-02-04 feat: Added tool that allow run circuits. Started development of web version of PC.
2024-02-05 feat: Added CommandCounter component,model,handler. Renamed dir features to widgets because logic also exists in entities.
2024-02-05 fix: Fixed delay after running hooks in elements models.
2024-02-05 feat: Added template for micro commands counter.
2024-02-15 feat: Added ROM element. Fixed passing args to hooks in scheme-environment tool.
